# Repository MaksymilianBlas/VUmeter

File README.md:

# VUmeter
Project with high hopes but never finished.
This was a project to create a VU meter to show something cool to my little brother. The design is made in KiCad, out of 2 PCBs that connect together via a pin header. The bottom PCB is the control circuitry, and the other one (which is vertical) contains rows of LEDs that should light up according to the loudness of the music, as well as a boost converter module. The control circuit has two main parts, a set of eight comparators that indicate the audio level, and eight simple op-amp constant current drivers that get enabled by the comparator outputs and drive the LEDs via a constant current. This was the main improvement over the similar design found in a video by GreatScott (https://www.youtube.com/watch?v=Jyrpx9rEGMI), where the LEDs are supplied from a constant voltage. 
Sadly, two errors have sneaked into the design: Firstly, the logic of the TLV3501 is inverted (it features a Shutdown pin, opposite to the Enable pin of the NCS2002 which was considered at the beginning of the design), and secondly, the comparators are missing pull-up resistors at the outputs (because they are LM393s, which have an open-drain output).
These errors have never been fixed due to lack of time and lost interest. Further possible improvements would be to use dual MOSFETs and quad comparators to save space on the PCB.

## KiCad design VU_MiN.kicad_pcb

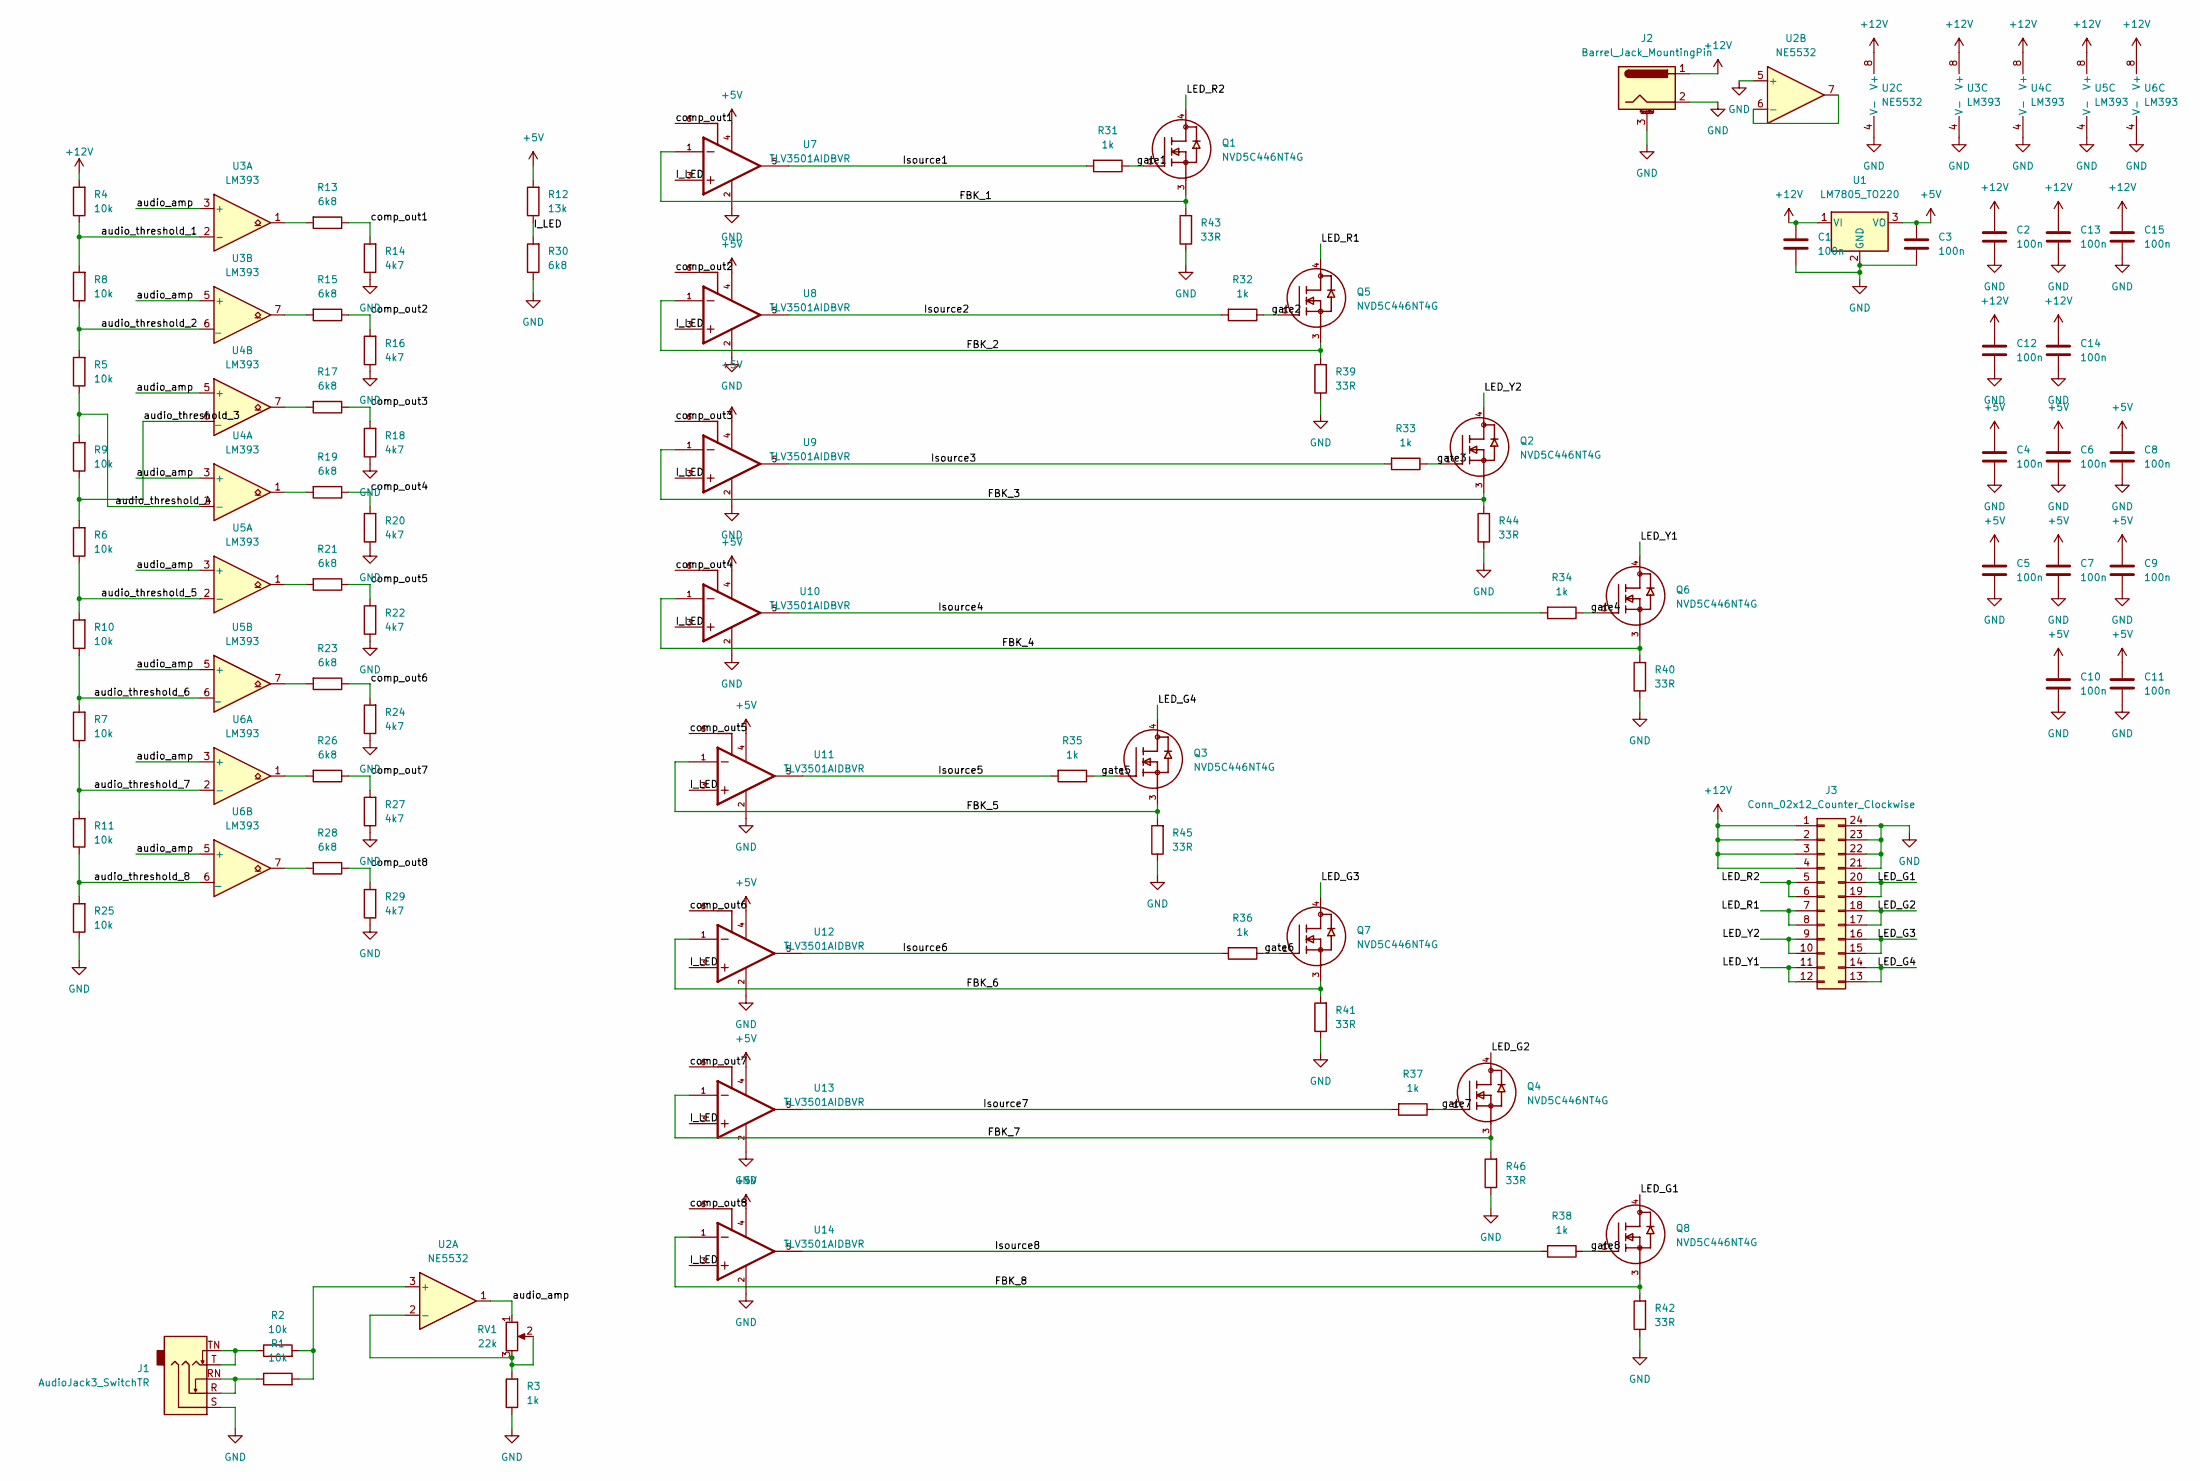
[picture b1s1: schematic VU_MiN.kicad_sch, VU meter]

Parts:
C1, C2, C3, C4, C5, C6, C7, C8, C9, C10, C11, C12, C13, C14, C15: 100n; C_0603_1608Metric_Pad1.08x0.95mm_HandSolder
J1: AudioJack3_SwitchTR; Jack_3.5mm_Ledino_KB3SPRS_Horizontal
J2: Barrel_Jack_MountingPin; BarrelJack_CUI_PJ-102AH_Horizontal
J3: Conn_02x12_Counter_Clockwise; PinSocket_2x12_P2.54mm_Vertical
Q1, Q2, Q3, Q4, Q5, Q6, Q7, Q8: NVD5C446NT4G; DPAK229P990X238-4N; PARTREV 0
R1, R2, R4, R5, R6, R7, R8, R9, R10, R11, R25: 10k; R_0603_1608Metric_Pad0.98x0.95mm_HandSolder
R3, R31, R32, R33, R34, R35, R36, R37, R38: 1k; R_0603_1608Metric_Pad0.98x0.95mm_HandSolder
R12: 13k; R_0603_1608Metric_Pad0.98x0.95mm_HandSolder
R13, R15, R17, R19, R21, R23, R26, R28, R30: 6k8; R_0603_1608Metric_Pad0.98x0.95mm_HandSolder
R14, R16, R18, R20, R22, R24, R27, R29: 4k7; R_0603_1608Metric_Pad0.98x0.95mm_HandSolder
R39, R40, R41, R42, R43, R44, R45, R46: 33R; R_1210_3225Metric_Pad1.30x2.65mm_HandSolder
RV1: 22k; Potentiometer_Alpha_RD901F-40-00D_Single_Vertical
U1: LM7805_TO220; TO-252-2
U2: NE5532; SOIC-8_3.9x4.9mm_P1.27mm
U3, U4, U5, U6: LM393; SO-8_3.9x4.9mm_P1.27mm
U7, U8, U9, U10, U11, U12, U13, U14: TLV3501AIDBVR; SOT95P280X145-6N; PARTREV E

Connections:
+5V: C3.1, C4.1, C5.1, C6.1, C7.1, C8.1, C9.1, C10.1, C11.1, R12.2, U1.3 (VO), U7.4, U8.4, U9.4, U10.4, U11.4, U12.4, U13.4, U14.4
+12V: C1.1, C2.1, C12.1, C13.1, C14.1, C15.1, J2.1, J3.1, J3.2, J3.3, J3.4, R4.2, U1.1 (VI), U2.8 (V+), U3.8 (V+), U4.8 (V+), U5.8 (V+), U6.8 (V+)
/FBK_1: Q1.3, R43.2, U7.1
/FBK_2: Q5.3, R39.2, U8.1
/FBK_3: Q2.3, R44.2, U9.1
/FBK_4: Q6.3, R40.2, U10.1
/FBK_5: Q3.3, R45.2, U11.1
/FBK_6: Q7.3, R41.2, U12.1
/FBK_7: Q4.3, R46.2, U13.1
/FBK_8: Q8.3, R42.2, U14.1
/I_LED: R12.1, R30.2, U7.3, U8.3, U9.3, U10.3, U11.3, U12.3, U13.3, U14.3
/Isource1: R31.2, U7.5
/Isource2: R32.2, U8.5
/Isource3: R33.2, U9.5
/Isource4: R34.2, U10.5
/Isource5: R35.2, U11.5
/Isource6: R36.2, U12.5
/Isource7: R37.2, U13.5
/Isource8: R38.2, U14.5
/LED_G1: J3.19, J3.20, Q8.4
/LED_G2: J3.17, J3.18, Q4.4
/LED_G3: J3.15, J3.16, Q7.4
/LED_G4: J3.13, J3.14, Q3.4
/LED_R1: J3.7, J3.8, Q5.4
/LED_R2: J3.5, J3.6, Q1.4
/LED_Y1: J3.11, J3.12, Q6.4
/LED_Y2: J3.9, J3.10, Q2.4
/audio_amp: RV1.1, U2.1, U3.3 (+), U3.5 (+), U4.3 (+), U4.5 (+), U5.3 (+), U5.5 (+), U6.3 (+), U6.5 (+)
/audio_threshold_1: R4.1, R8.2, U3.2 (-)
/audio_threshold_2: R5.2, R8.1, U3.6 (_)
/audio_threshold_3: R6.2, R9.1, U4.6 (_)
/audio_threshold_4: R5.1, R9.2, U4.2 (-)
/audio_threshold_5: R6.1, R10.2, U5.2 (-)
/audio_threshold_6: R7.2, R10.1, U5.6 (_)
/audio_threshold_7: R7.1, R11.2, U6.2 (-)
/audio_threshold_8: R11.1, R25.2, U6.6 (_)
/comp_out1: R13.1, R14.2, U7.6
/comp_out2: R15.1, R16.2, U8.6
/comp_out3: R17.1, R18.2, U9.6
/comp_out4: R19.1, R20.2, U10.6
/comp_out5: R21.1, R22.2, U11.6
/comp_out6: R23.1, R24.2, U12.6
/comp_out7: R26.1, R27.2, U13.6
/comp_out8: R28.1, R29.2, U14.6
/gate1: Q1.1, R31.1
/gate2: Q5.1, R32.1
/gate3: Q2.1, R33.1
/gate4: Q6.1, R34.1
/gate5: Q3.1, R35.1
/gate6: Q7.1, R36.1
/gate7: Q4.1, R37.1
/gate8: Q8.1, R38.1
GND: C1.2, C2.2, C3.2, C4.2, C5.2, C6.2, C7.2, C8.2, C9.2, C10.2, C11.2, C12.2, C13.2, C14.2, C15.2, J1.S, J2.2, J2.3 (MountPin), J3.21, J3.22, J3.23, J3.24, R3.1, R14.1, R16.1, R18.1, R20.1, R22.1, R24.1, R25.1, R27.1, R29.1, R30.1, R39.1, R40.1, R41.1, R42.1, R43.1, R44.1, R45.1, R46.1, U1.2 (GND), U2.4 (V-), U2.5 (+), U3.4 (V-), U4.4 (V-), U5.4 (V-), U6.4 (V-), U7.2, U8.2, U9.2, U10.2, U11.2, U12.2, U13.2, U14.2
unnamed: J1.R, J1.RN, R1.1
unnamed: J1.T, J1.TN, R2.1
unnamed: R1.2, R2.2, U2.3 (+)
unnamed: R3.2, RV1.2, RV1.3, U2.2 (-)
unnamed: R13.2, U3.1
unnamed: R15.2, U3.7
unnamed: R17.2, U4.7
unnamed: R19.2, U4.1
unnamed: R21.2, U5.1
unnamed: R23.2, U5.7
unnamed: R26.2, U6.1
unnamed: R28.2, U6.7
unnamed: U2.6 (-), U2.7

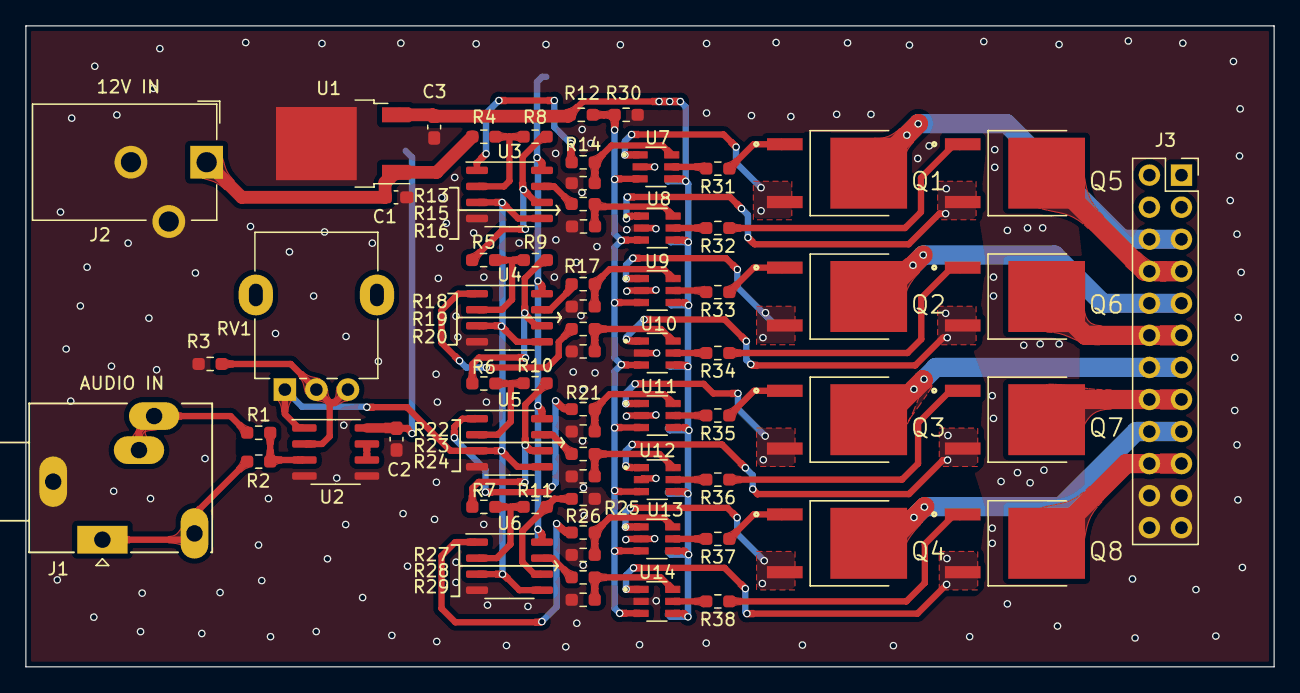
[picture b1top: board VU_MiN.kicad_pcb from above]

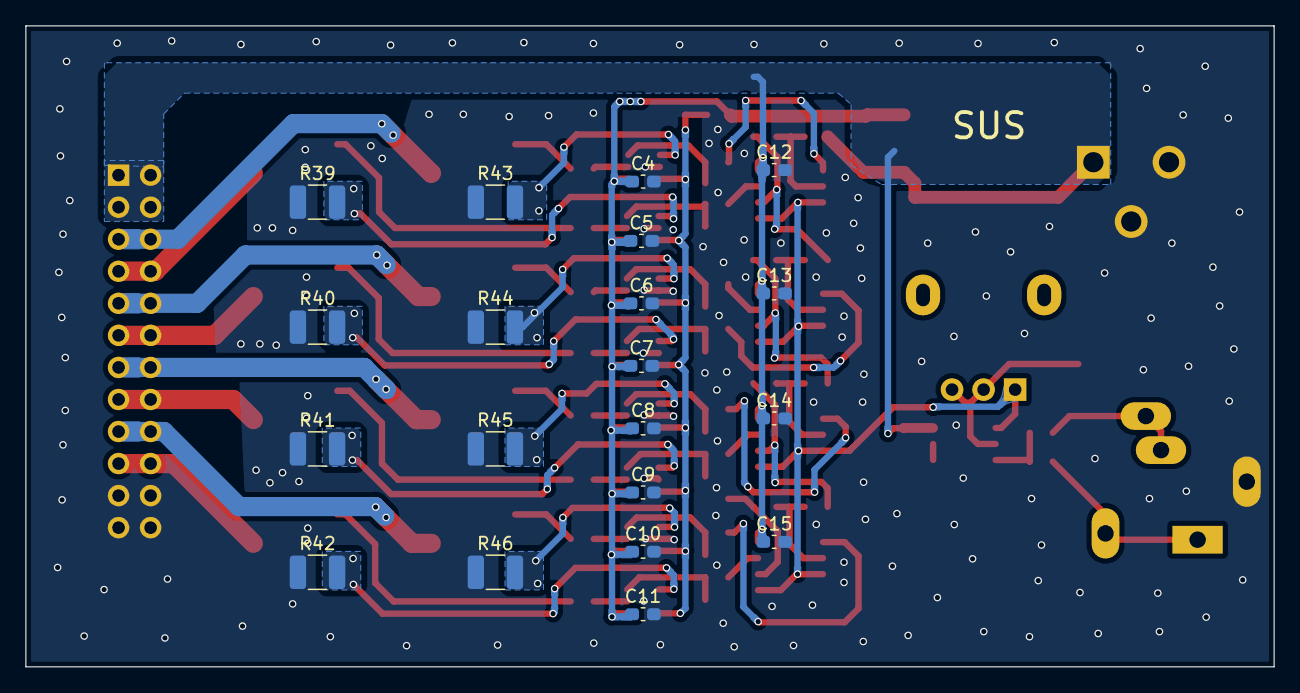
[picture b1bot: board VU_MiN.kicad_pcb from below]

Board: 2 copper layers, 98.9 x 50.8 mm, 87 parts (20 on the bottom side), 66 nets.

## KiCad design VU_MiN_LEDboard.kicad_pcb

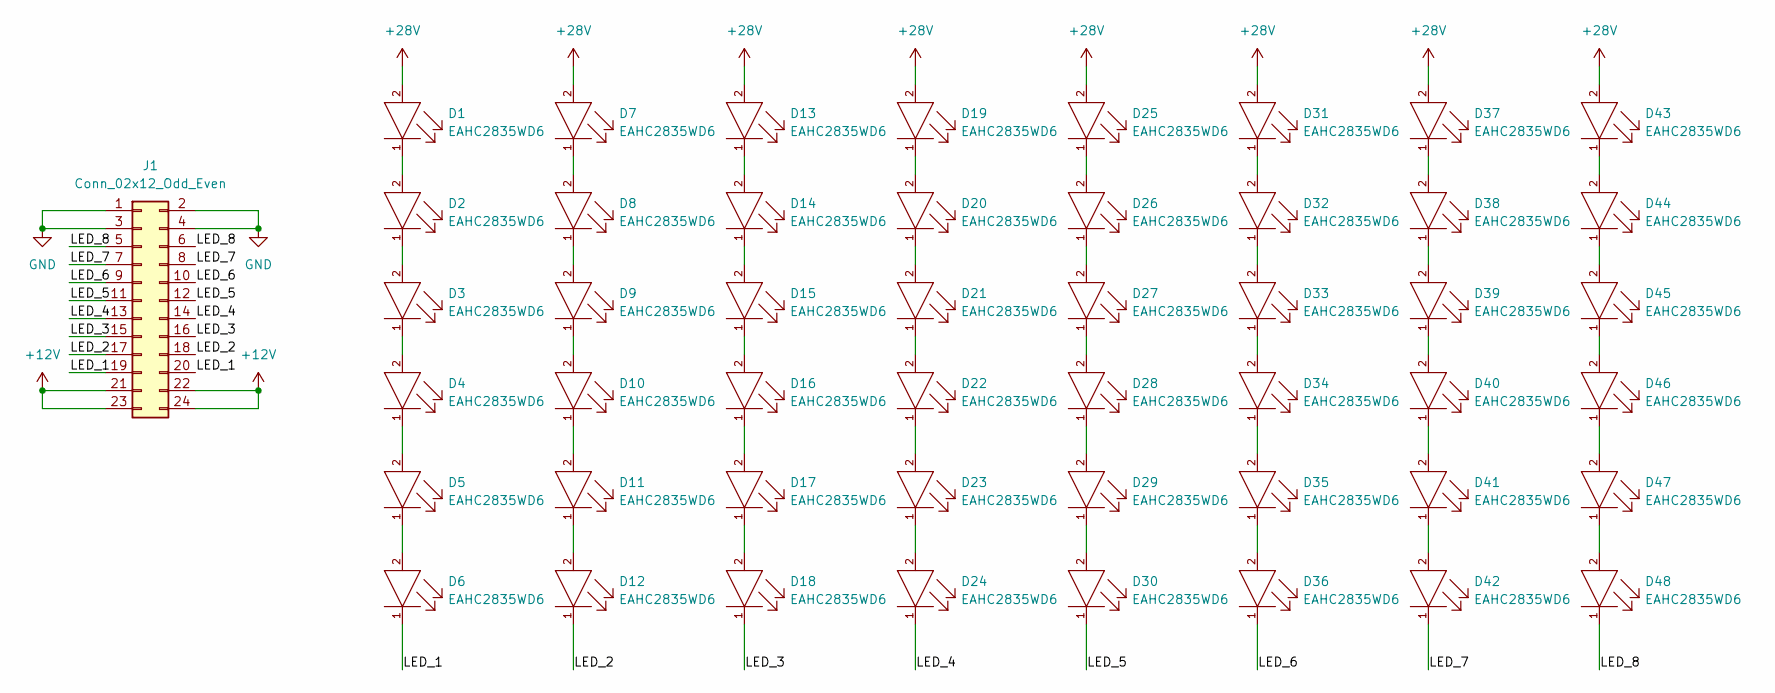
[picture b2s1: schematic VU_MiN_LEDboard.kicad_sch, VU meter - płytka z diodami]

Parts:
D1, D2, D3, D4, D5, D6, D7, D8, D9, D10, D11, D12, D13, D14, D15, D16, D17, D18, D19, D20, D21, D22, D23, D24, D25, D26, D27, D28, D29, D30, D31, D32, D33, D34, D35, D36, D37, D38, D39, D40, D41, D42, D43, D44, D45, D46, D47, D48: EAHC2835WD6; Everlight-EAHC2835WD6-MFG; forward voltage 3.4V; reverse voltage 5V; mouser part number 638-EAHC2835WD6; digikey description LED COOL WHITE 6500K 2SMD
J1: Conn_02x12_Odd_Even; PinHeader_2x12_P2.54mm_Horizontal

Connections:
+12V: J1.21, J1.22, J1.23, J1.24; also elsewhere on the board
+28V: D1.2 (ANODE), D7.2 (ANODE), D13.2 (ANODE), D19.2 (ANODE), D25.2 (ANODE), D31.2 (ANODE), D37.2 (ANODE), D43.2 (ANODE)
/LED_1: D6.1 (CATHODE), J1.19, J1.20
/LED_2: D12.1 (CATHODE), J1.17, J1.18
/LED_3: D18.1 (CATHODE), J1.15, J1.16
/LED_4: D24.1 (CATHODE), J1.13, J1.14
/LED_5: D30.1 (CATHODE), J1.11, J1.12
/LED_6: D36.1 (CATHODE), J1.9, J1.10
/LED_7: D42.1 (CATHODE), J1.7, J1.8
/LED_8: D48.1 (CATHODE), J1.5, J1.6
GND: J1.1, J1.2, J1.3, J1.4
unnamed: D1.1 (CATHODE), D2.2 (ANODE)
unnamed: D2.1 (CATHODE), D3.2 (ANODE)
unnamed: D3.1 (CATHODE), D4.2 (ANODE)
unnamed: D4.1 (CATHODE), D5.2 (ANODE)
unnamed: D5.1 (CATHODE), D6.2 (ANODE)
unnamed: D7.1 (CATHODE), D8.2 (ANODE)
unnamed: D8.1 (CATHODE), D9.2 (ANODE)
unnamed: D10.1 (CATHODE), D11.2 (ANODE)
unnamed: D9.1 (CATHODE), D10.2 (ANODE)
unnamed: D11.1 (CATHODE), D12.2 (ANODE)
unnamed: D13.1 (CATHODE), D14.2 (ANODE)
unnamed: D14.1 (CATHODE), D15.2 (ANODE)
unnamed: D15.1 (CATHODE), D16.2 (ANODE)
unnamed: D16.1 (CATHODE), D17.2 (ANODE)
unnamed: D17.1 (CATHODE), D18.2 (ANODE)
unnamed: D19.1 (CATHODE), D20.2 (ANODE)
unnamed: D20.1 (CATHODE), D21.2 (ANODE)
unnamed: D21.1 (CATHODE), D22.2 (ANODE)
unnamed: D22.1 (CATHODE), D23.2 (ANODE)
unnamed: D23.1 (CATHODE), D24.2 (ANODE)
unnamed: D25.1 (CATHODE), D26.2 (ANODE)
unnamed: D26.1 (CATHODE), D27.2 (ANODE)
unnamed: D27.1 (CATHODE), D28.2 (ANODE)
unnamed: D28.1 (CATHODE), D29.2 (ANODE)
unnamed: D29.1 (CATHODE), D30.2 (ANODE)
unnamed: D31.1 (CATHODE), D32.2 (ANODE)
unnamed: D32.1 (CATHODE), D33.2 (ANODE)
unnamed: D33.1 (CATHODE), D34.2 (ANODE)
unnamed: D34.1 (CATHODE), D35.2 (ANODE)
unnamed: D35.1 (CATHODE), D36.2 (ANODE)
unnamed: D37.1 (CATHODE), D38.2 (ANODE)
unnamed: D38.1 (CATHODE), D39.2 (ANODE)
unnamed: D39.1 (CATHODE), D40.2 (ANODE)
unnamed: D40.1 (CATHODE), D41.2 (ANODE)
unnamed: D41.1 (CATHODE), D42.2 (ANODE)
unnamed: D43.1 (CATHODE), D44.2 (ANODE)
unnamed: D44.1 (CATHODE), D45.2 (ANODE)
unnamed: D45.1 (CATHODE), D46.2 (ANODE)
unnamed: D46.1 (CATHODE), D47.2 (ANODE)
unnamed: D47.1 (CATHODE), D48.2 (ANODE)

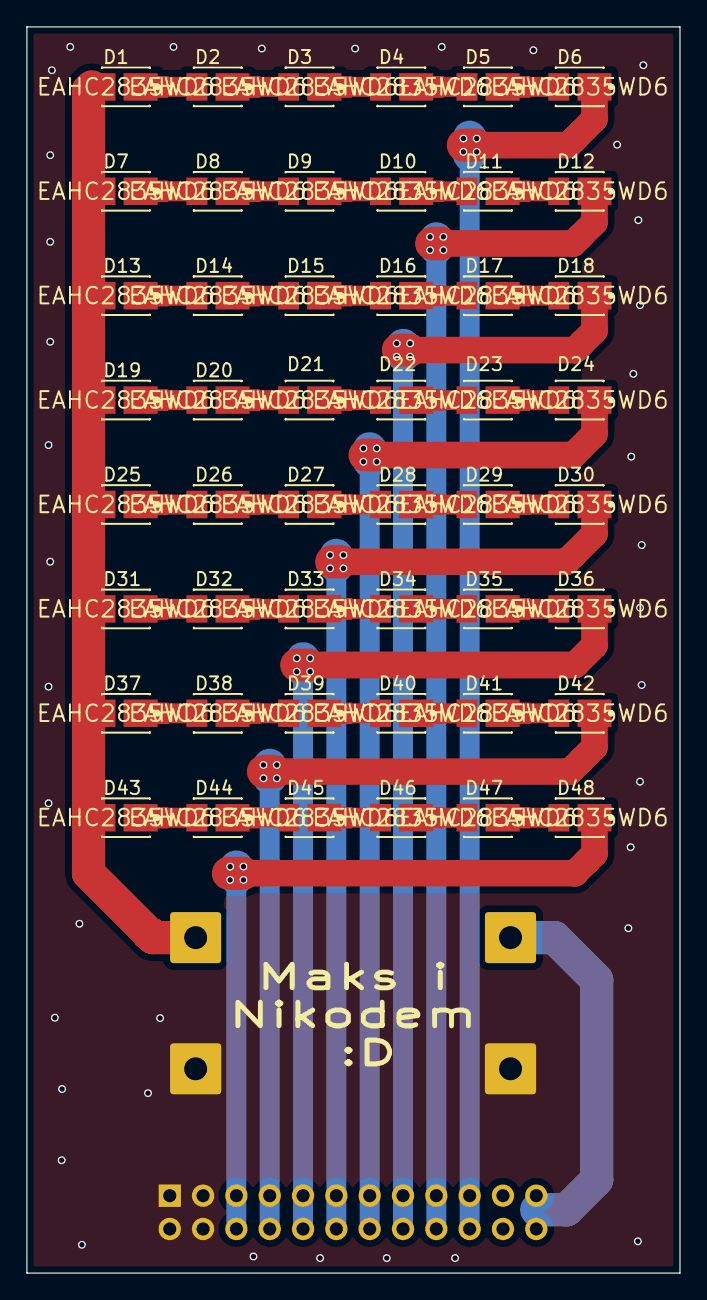
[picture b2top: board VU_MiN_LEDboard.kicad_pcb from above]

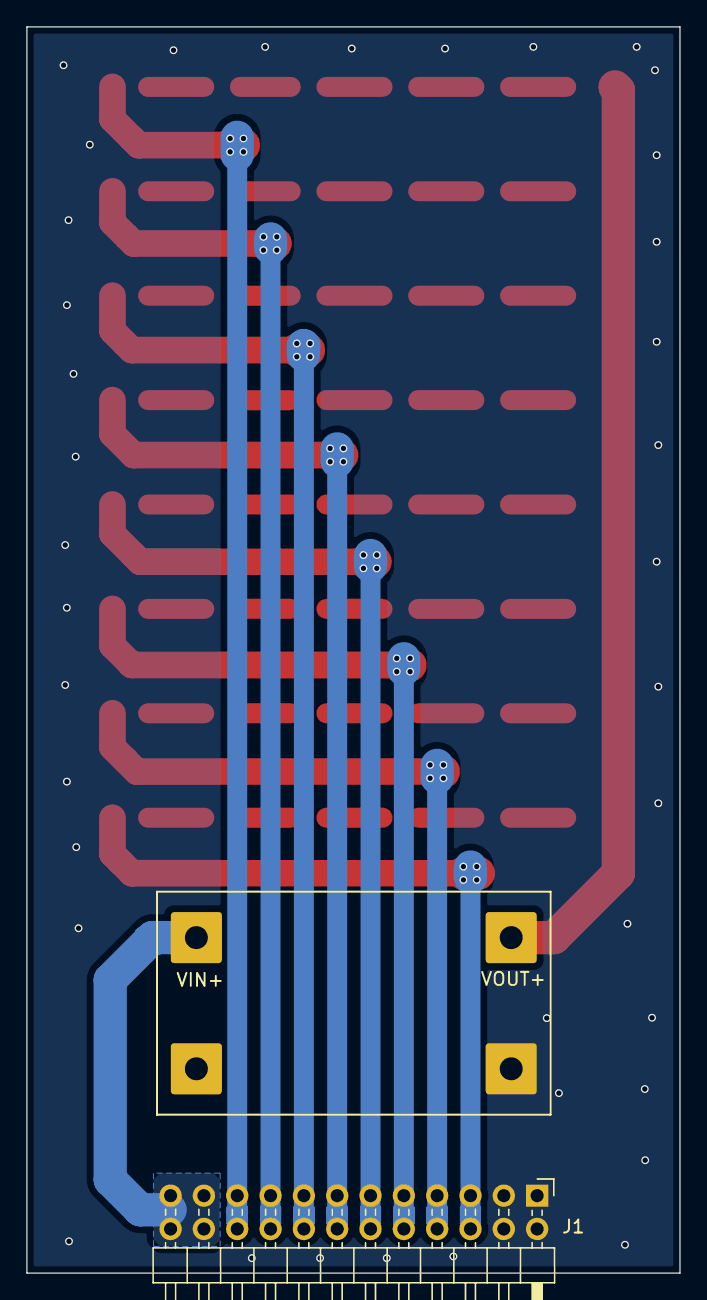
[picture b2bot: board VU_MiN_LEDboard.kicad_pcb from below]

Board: 2 copper layers, 49.8 x 95.0 mm, 50 parts (2 on the bottom side), 51 nets.

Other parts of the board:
VOUT+: SolderWire-1sqmm_1x01_D1.4mm_OD3.9mm

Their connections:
+12V: VOUT+.1; also elsewhere on the board

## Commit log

2025-03-03 Add files via upload
    Add project files for the LED PCB.
2025-03-03 Add files via upload
    Add project files for controll PCB.
